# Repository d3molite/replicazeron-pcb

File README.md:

This is an extension project to the replicazeron repository by [9R](https://github.com/9R/replicazeron/tree/main). 

I wanted a custom made PCB to allow for easier wiring. 
Once I have built mine, I will update this doc with a BOM of parts that you will need. 

I opted for SMT Diodes due to space reasons.

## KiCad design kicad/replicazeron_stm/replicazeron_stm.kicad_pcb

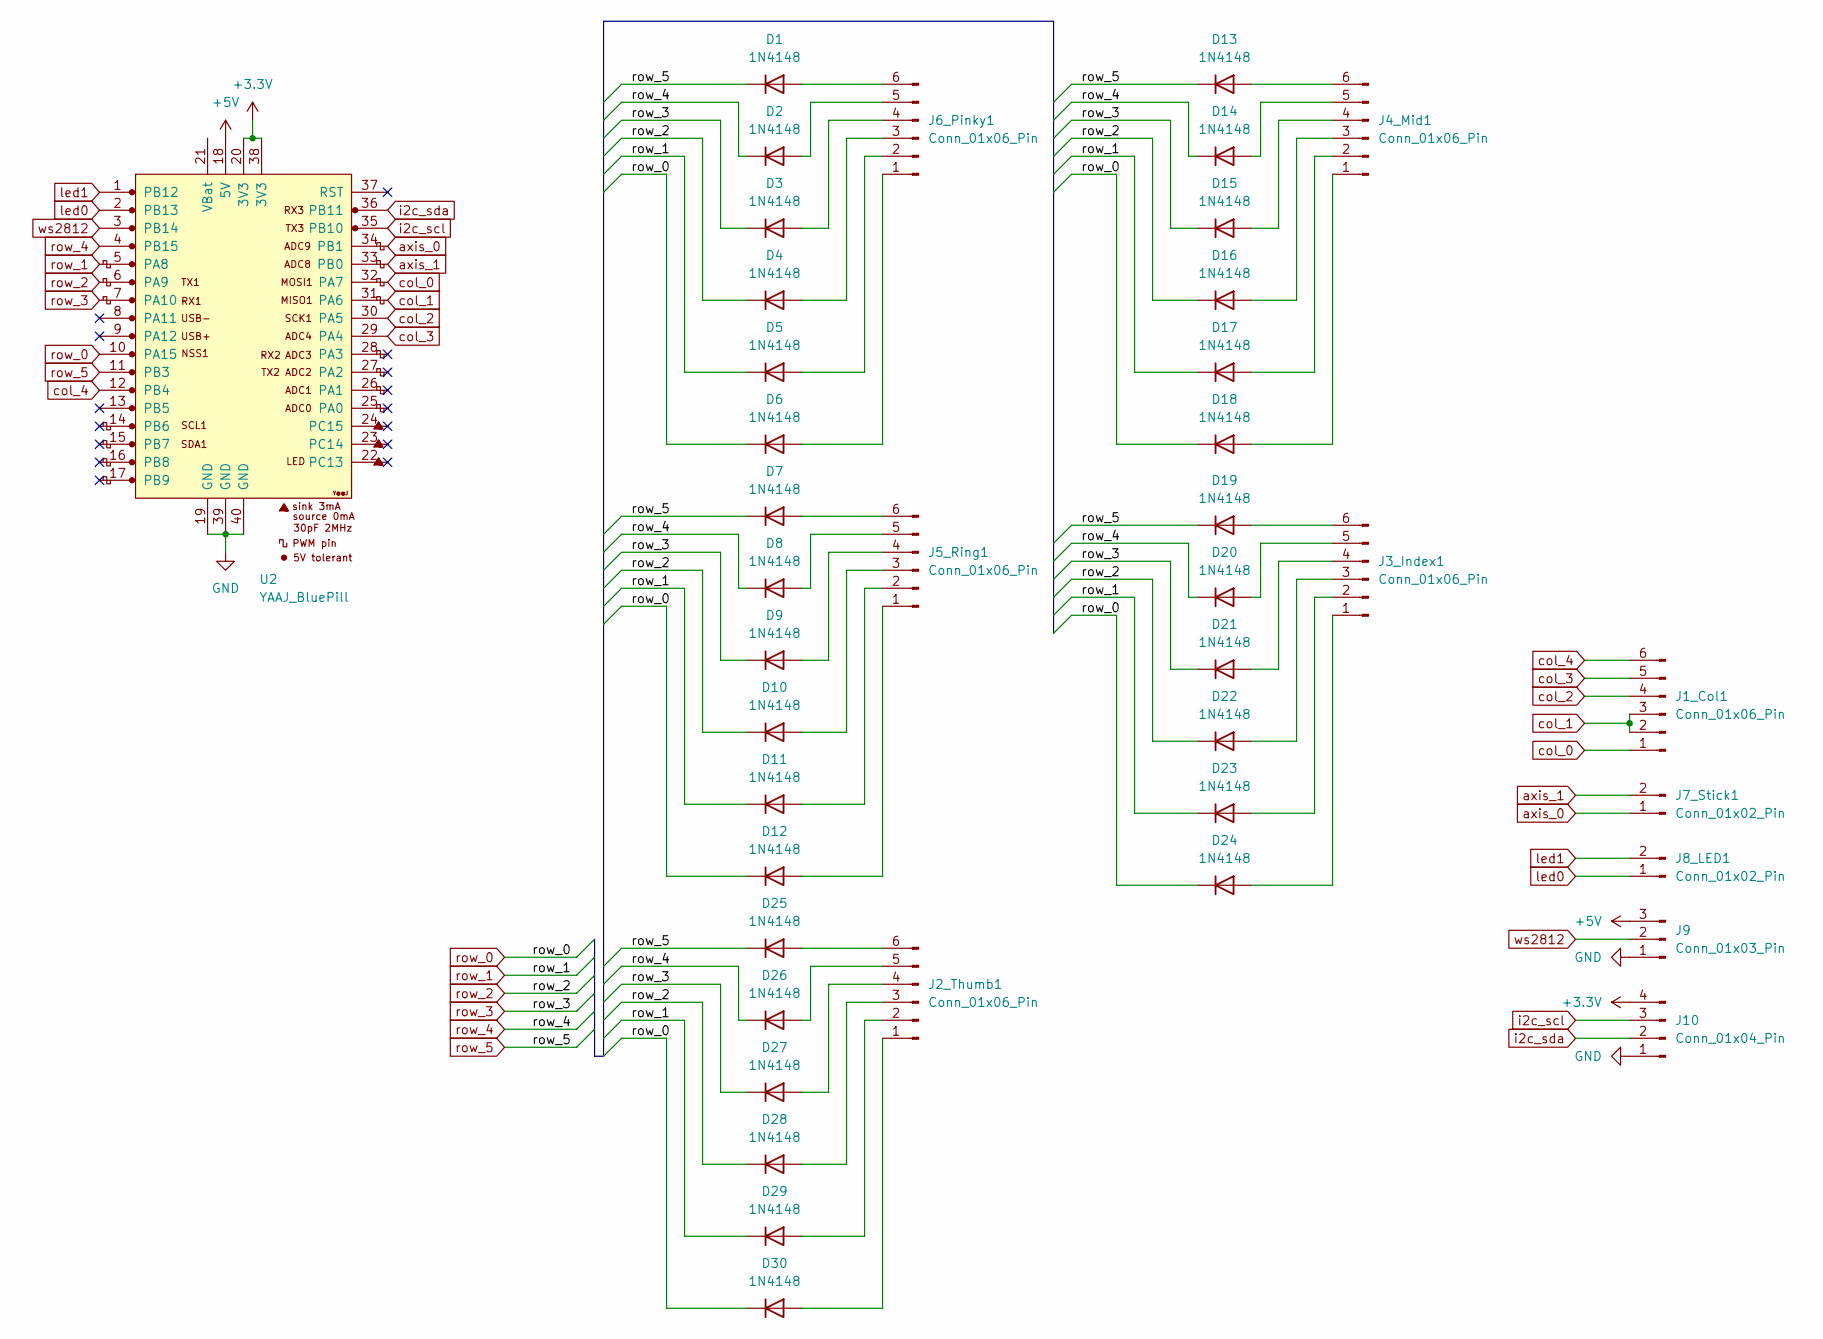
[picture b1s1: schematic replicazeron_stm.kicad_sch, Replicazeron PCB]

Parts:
D1, D2, D3, D4, D5, D6, D7, D8, D9, D10, D11, D12, D13, D14, D15, D16, D17, D18, D19, D20, D21, D22, D23, D24, D25, D26, D27, D28, D29, D30: 1N4148; D_SOD-323F
J1_Col1, J2_Thumb1, J3_Index1, J4_Mid1, J5_Ring1, J6_Pinky1: Conn_01x06_Pin; JST_XH_B6B-XH-A_1x06_P2.50mm_Vertical
J7_Stick1, J8_LED1: Conn_01x02_Pin; JST_XH_B2B-XH-A_1x02_P2.50mm_Vertical
J9: Conn_01x03_Pin; JST_XH_B3B-XH-A_1x03_P2.50mm_Vertical
J10: Conn_01x04_Pin; JST_XH_B4B-XH-A_1x04_P2.50mm_Vertical
U2: YAAJ_BluePill; YAAJ_BluePill_1

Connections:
+3.3V: J10.4, U2.20 (3V3), U2.38 (3V3)
+5V: J9.3, U2.18 (5V)
GND: J9.1, J10.1, U2.19 (GND), U2.39 (GND), U2.40 (GND)
unnamed: D1.2 (A), J6_Pinky1.6
unnamed: D2.2 (A), J6_Pinky1.5
unnamed: D3.2 (A), J6_Pinky1.4
unnamed: D4.2 (A), J6_Pinky1.3
unnamed: D5.2 (A), J6_Pinky1.2
unnamed: D6.2 (A), J6_Pinky1.1
unnamed: D7.2 (A), J5_Ring1.6
unnamed: D8.2 (A), J5_Ring1.5
unnamed: D9.2 (A), J5_Ring1.4
unnamed: D10.2 (A), J5_Ring1.3
unnamed: D11.2 (A), J5_Ring1.2
unnamed: D12.2 (A), J5_Ring1.1
unnamed: D13.2 (A), J4_Mid1.6
unnamed: D14.2 (A), J4_Mid1.5
unnamed: D15.2 (A), J4_Mid1.4
unnamed: D16.2 (A), J4_Mid1.3
unnamed: D17.2 (A), J4_Mid1.2
unnamed: D18.2 (A), J4_Mid1.1
unnamed: D19.2 (A), J3_Index1.6
unnamed: D20.2 (A), J3_Index1.5
unnamed: D21.2 (A), J3_Index1.4
unnamed: D22.2 (A), J3_Index1.3
unnamed: D23.2 (A), J3_Index1.2
unnamed: D24.2 (A), J3_Index1.1
unnamed: D25.2 (A), J2_Thumb1.6
unnamed: D26.2 (A), J2_Thumb1.5
unnamed: D27.2 (A), J2_Thumb1.4
unnamed: D28.2 (A), J2_Thumb1.3
unnamed: D29.2 (A), J2_Thumb1.2
unnamed: D30.2 (A), J2_Thumb1.1
axis_0: J7_Stick1.1, U2.34 (PB1)
axis_1: J7_Stick1.2, U2.33 (PB0)
col_0: J1_Col1.1, U2.32 (PA7)
col_1: J1_Col1.2, J1_Col1.3, U2.31 (PA6)
col_2: J1_Col1.4, U2.30 (PA5)
col_3: J1_Col1.5, U2.29 (PA4)
col_4: J1_Col1.6, U2.12 (PB4)
i2c_scl: J10.3, U2.35 (PB10)
i2c_sda: J10.2, U2.36 (PB11)
led0: J8_LED1.1, U2.2 (PB13)
led1: J8_LED1.2, U2.1 (PB12)
row_0: D6.1 (K), D12.1 (K), D18.1 (K), D24.1 (K), D30.1 (K), U2.10 (PA15)
row_1: D5.1 (K), D11.1 (K), D17.1 (K), D23.1 (K), D29.1 (K), U2.5 (PA8)
row_2: D4.1 (K), D10.1 (K), D16.1 (K), D22.1 (K), D28.1 (K), U2.6 (PA9)
row_3: D3.1 (K), D9.1 (K), D15.1 (K), D21.1 (K), D27.1 (K), U2.7 (PA10)
row_4: D2.1 (K), D8.1 (K), D14.1 (K), D20.1 (K), D26.1 (K), U2.4 (PB15)
row_5: D1.1 (K), D7.1 (K), D13.1 (K), D19.1 (K), D25.1 (K), U2.11 (PB3)
ws2812: J9.2, U2.3 (PB14)

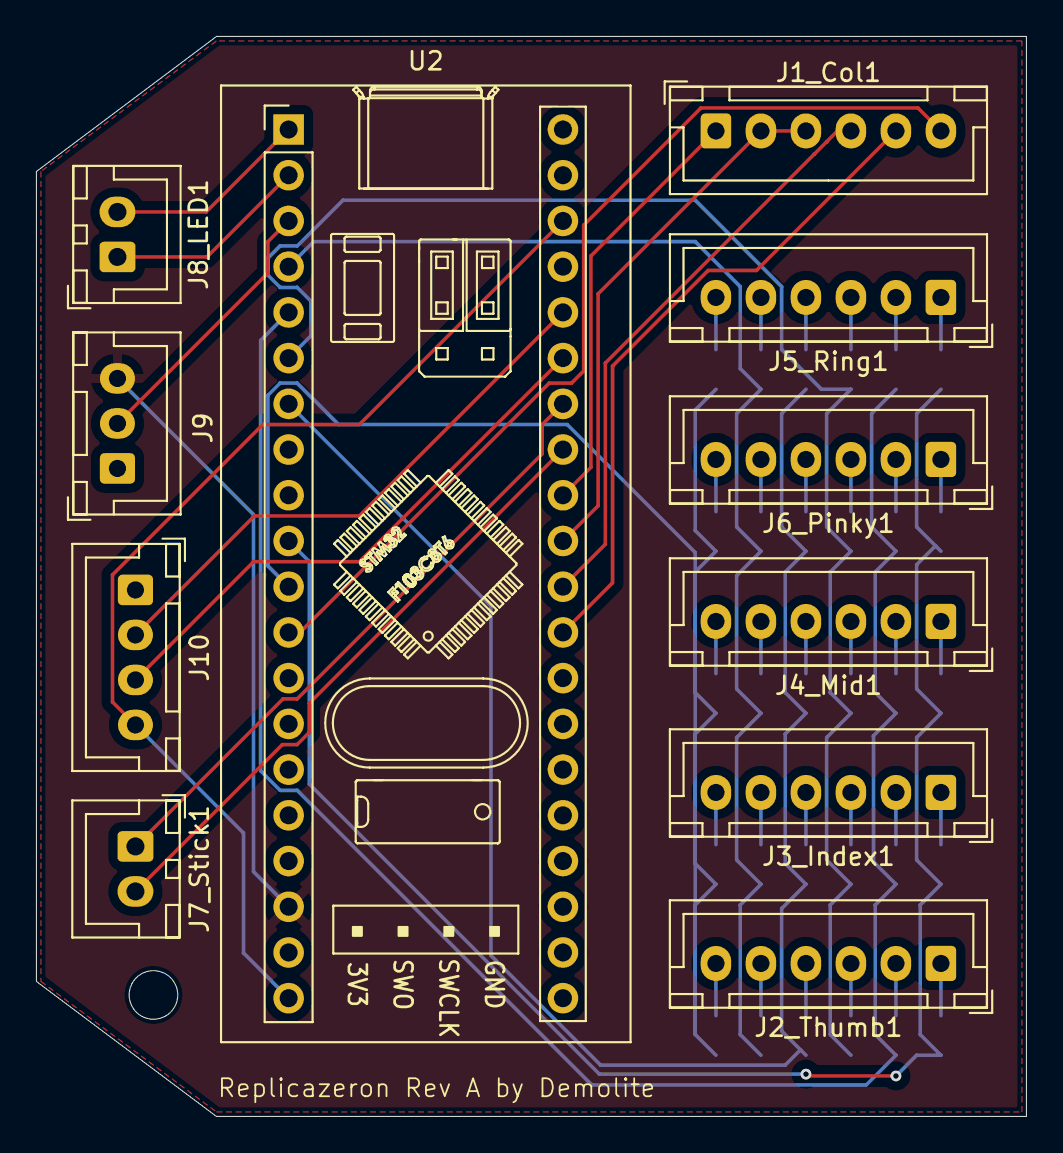
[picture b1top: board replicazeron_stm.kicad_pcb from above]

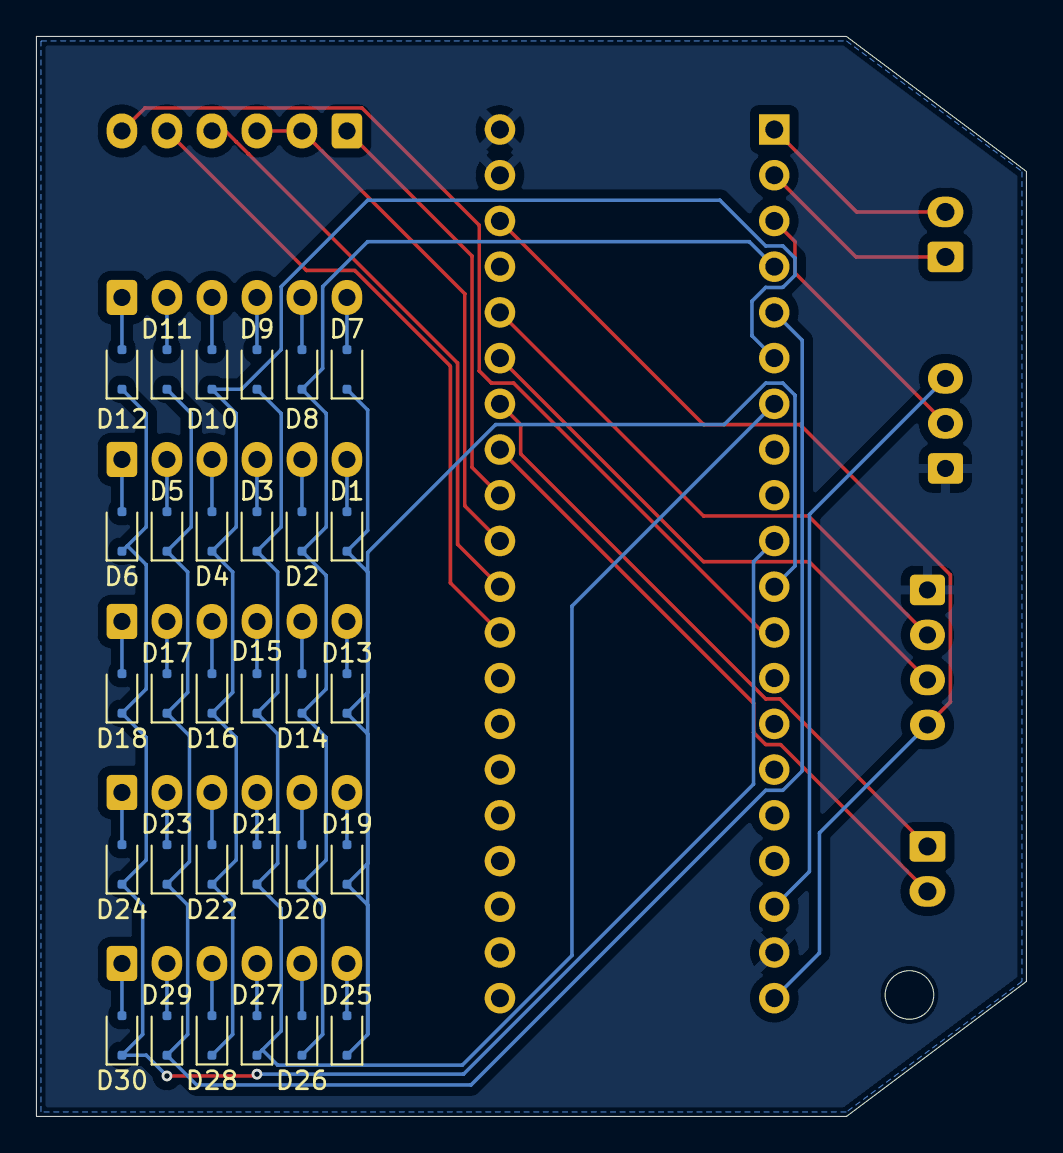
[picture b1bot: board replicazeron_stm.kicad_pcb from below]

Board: 2 copper layers, 55.0 x 60.0 mm, 41 parts (30 on the bottom side), 51 nets.

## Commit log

2026-01-16 Pre Routing PCB Version A
2026-01-16 Readme Updates
2026-01-16 Routing PCB Version A
2026-01-16 Fabrication Files Version A
